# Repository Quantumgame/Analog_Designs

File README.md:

# This repo stores various public analog designs I work on over the years

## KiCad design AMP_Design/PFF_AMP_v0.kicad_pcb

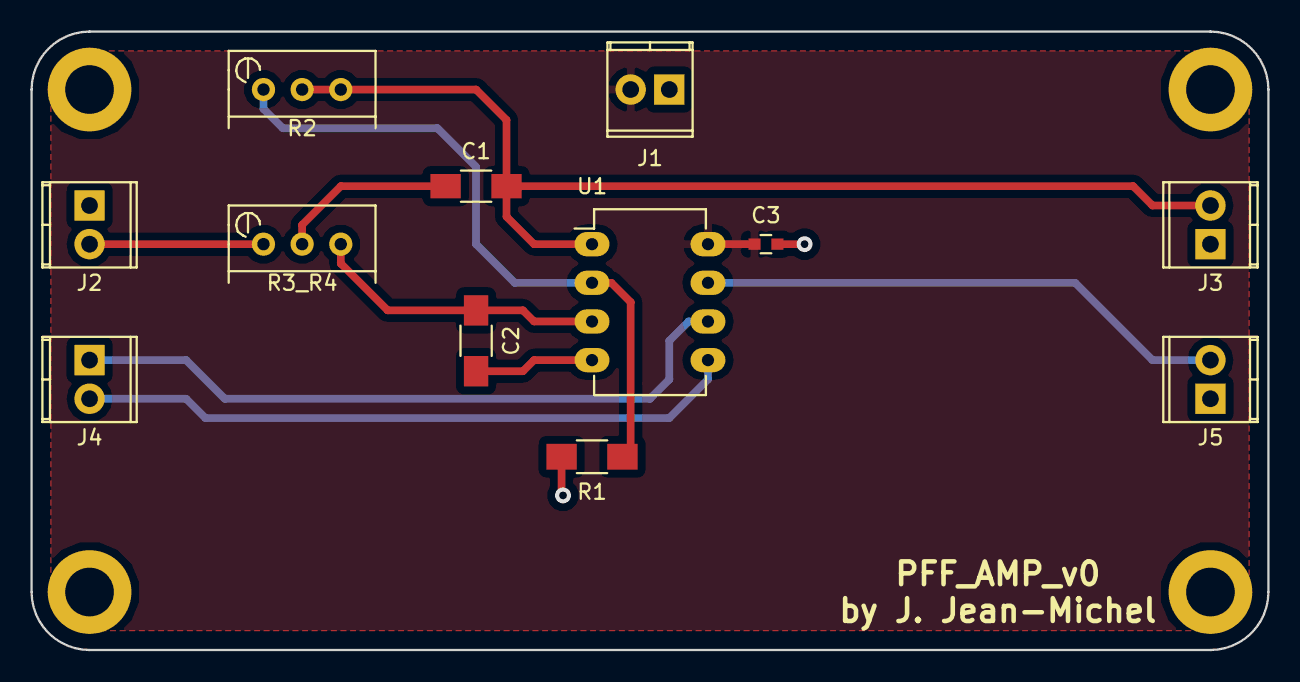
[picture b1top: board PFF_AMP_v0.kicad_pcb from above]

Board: 2 copper layers, 81.3 x 40.6 mm, 12 parts (0 on the bottom side), 10 nets.

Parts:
C1, C2: 3.3nF; C_1206_HandSoldering
C3: 10uF; C_0603
J1, J2, J3, J4, J5: CONN_01X02; TerminalBlock_Pheonix_MPT-2.54mm_2pol
R1: 10k; R_1206_HandSoldering
R2, R3_R4: 100k; Potentiometer_Bourns_3296W_3-8Zoll_Inline_ScrewUp
U1: MCP6002; DIP-8_W7.62mm_LongPads

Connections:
+5V: C3.1, J1.2, U1.8
/Analog_IN: J2.2, R3_R4.1
/Analog_OUT: C1.2, J3.2, R2.2, R2.3, U1.1
GND: C2.2, C3.2, J1.1, J2.1, J3.1, J5.1, R1.2, U1.4
unnamed: C1.1, R3_R4.2
unnamed: C2.1, R3_R4.3, U1.3
unnamed: J4.1, U1.6
unnamed: J4.2, U1.5
unnamed: J5.2, U1.7
unnamed: R1.1, R2.1, U1.2

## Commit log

2016-11-29 Design Files for PFF interview quiz
